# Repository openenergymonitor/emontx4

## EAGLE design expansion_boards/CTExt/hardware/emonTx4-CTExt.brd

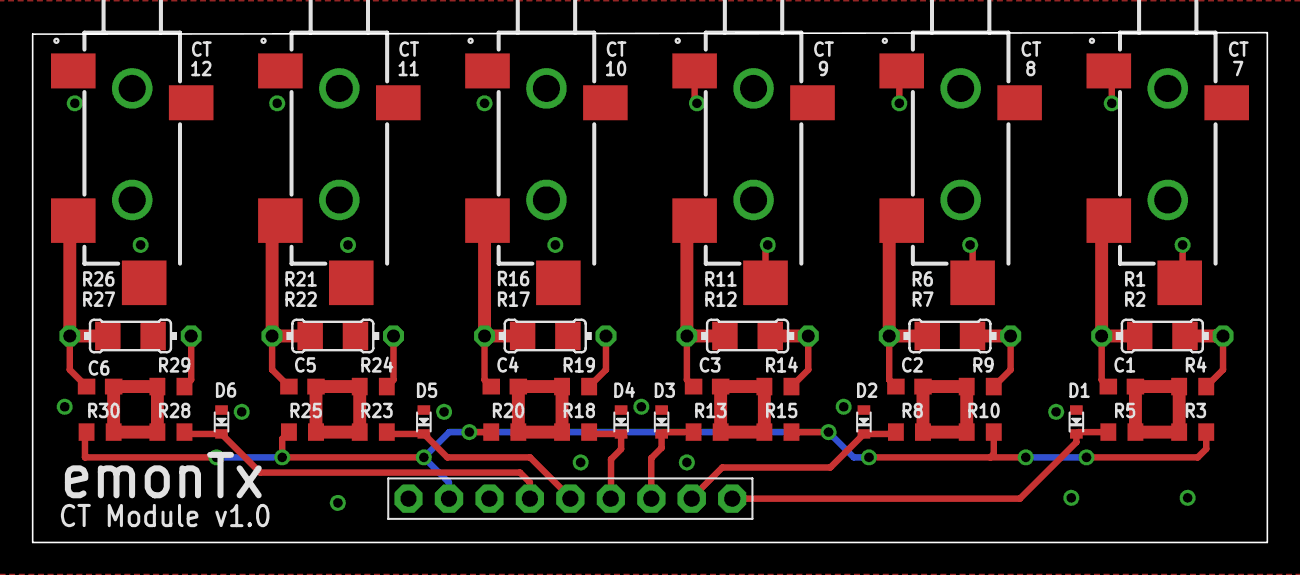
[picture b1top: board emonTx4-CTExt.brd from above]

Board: 2 copper layers, 77.5 x 32.0 mm, 49 parts (0 on the bottom side), 20 nets.

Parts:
ANALOG_EXPANDER: 1X09-BIG
C1, C2, C3, C4, C5, C6: 10uF 6V; C0603
D1, D2, D3, D4, D5, D6: ESD5Z3.3T1G; SOD-523
J1, J2, J3, J4, J7, J8: SJ-3524-SMT-TR
R1, R7, R12, R17, R22, R27: R1206
R2, R6, R11, R16, R21, R26: 0204/7
R3, R10, R15, R20, R25, R30: 180k; R0603
R4, R9, R14, R19, R24, R29: 33k; R0603
R5, R8, R13, R18, R23, R28: 1k; R0603

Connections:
3.3V: ANALOG_EXPANDER.2, R3.2, R10.2, R15.2, R20.2, R25.2, R30.2
AGND: ANALOG_EXPANDER.1, D1.A, D2.A, D3.A, D4.A, D5.A, D6.A, J1.1, J1.4, J2.1, J2.4, J3.1, J3.4, J4.1, J4.4, J7.1, J7.4, J8.1, J8.4, R1.1, R2.1, R4.2, R6.1, R7.1, R9.2, R11.1, R12.1, R14.2, R16.1, R17.1, R19.2, R21.1, R22.1, R24.2, R26.1, R27.1, R29.2
CT7: ANALOG_EXPANDER.9, D1.K, R5.2
CT8: ANALOG_EXPANDER.8, D2.K, R8.2
CT9: ANALOG_EXPANDER.7, D3.K, R13.2
CT10: ANALOG_EXPANDER.6, D4.K, R18.2
CT11: ANALOG_EXPANDER.5, D5.K, R23.2
CT12: ANALOG_EXPANDER.4, D6.K, R28.2
unnamed: C2.1, J2.2, R6.2, R7.2
unnamed: C2.2, R8.1, R9.1, R10.1
unnamed: C3.1, J4.2, R11.2, R12.2
unnamed: C3.2, R13.1, R14.1, R15.1
unnamed: C4.1, J7.2, R16.2, R17.2
unnamed: C4.2, R18.1, R19.1, R20.1
unnamed: C5.1, J8.2, R21.2, R22.2
unnamed: C5.2, R23.1, R24.1, R25.1
unnamed: C6.1, J3.2, R26.2, R27.2
unnamed: C6.2, R28.1, R29.1, R30.1
unnamed: C1.2, R3.1, R4.1, R5.1
unnamed: C1.1, J1.2, R1.2, R2.2

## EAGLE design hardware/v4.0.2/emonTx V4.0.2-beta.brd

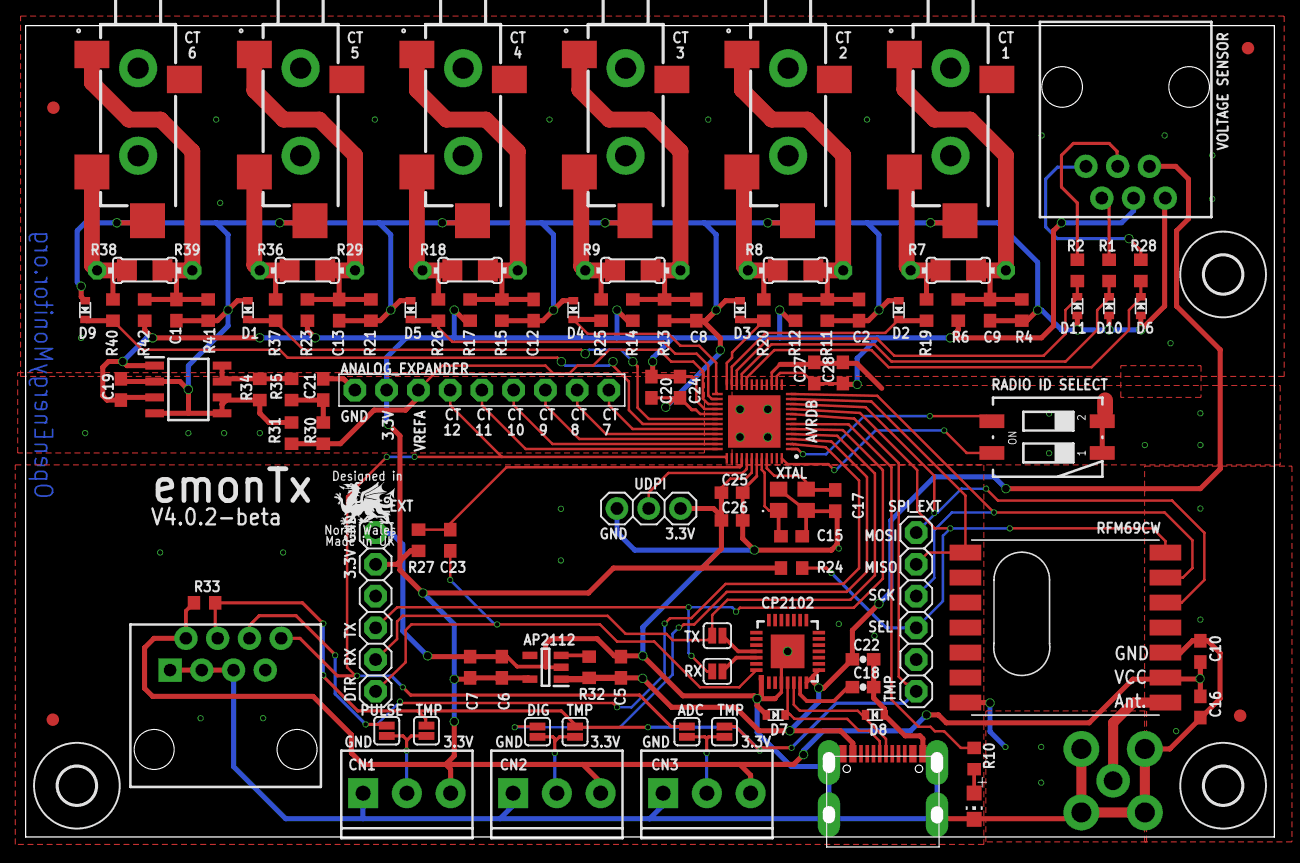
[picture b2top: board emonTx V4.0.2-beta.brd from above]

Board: 2 copper layers, 99.9 x 64.9 mm, 118 parts (1 on the bottom side), 65 nets.

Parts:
ANALOG_EXPANDER: 1X09-BIG
AP2112: AP2112K-3.3TRG1; SOT95P282X130-5N
AVRDB: AVR128DB48T-E_6LX; QFN40P600X600X90-49N
C1, C2, C8, C9, C12, C13: 10uF 6V; C0603
C5, C6: 1uF 6V; C0603
C7, C10, C20, C23, C25, C27: 100nF; C0603
C15, C17: 22pF; C0603
C16: 10uF; C0603
C18, C22: 100nF; 0603-CAP
C19, C21: 2.2uF; C0603
C24, C26, C28: 1uF; C0603
CN1, CN2, CN3: SCREWTERMINAL-3.5MM-3
CP2102: CP210X_USB_UART; MLP28
D1, D2, D3, D4, D5, D7, D8, D9: ESD5Z3.3T1G; SOD-523
D6, D10, D11: ESD; SOD-523
H2, H3, H4: MOUNT-HOLE3.0; 3,0
IC1: MCP1501-10E_SN; SOIC127P600X175-8N
J1, J2, J3, J4, J7, J8: SJ-3524-SMT-TR
J9: RJ11; RJ11-6
JP1: 1X06
LED1: Red 1.85V; CHIP-LED0805
LOGO1: OSHW_LOGO_6MILX0200-NT; OSHW_6X200_NOTEXT
R1, R2, R10, R28: 1K; R0603
R3, R5, R16, R22, R29, R38: 0204/7
R4, R11, R13, R15, R21, R41: 3.3k; R0603
R6, R12, R14, R17, R23, R42: 18k; R0603
R7, R8, R9, R18, R36, R39: R1206
R19, R20, R25, R26, R37, R40: 1k; R0603
R24: 120K; R0603
R27, R30, R31, R34: 10k; R0603
R32: 10K; R0603
R33: 4K7; R0603
R35: 10R; R0603
RX: SOLDERJUMPERNC; SJ_2S
S3: 2_SMT_DIP_SWITCH; DIP_SWITCH_SMT
SPI_EXT: 1X06
TX: SOLDERJUMPERNC; SJ_2S
TX_LINK1, TX_LINK2, TX_LINK3, TX_LINK4, TX_LINK5, TX_LINK6: SOLDERJUMPERNC; SJ_2S
U$1, U$4, U$5, U$7: FIDUCIAL; FIDUCIAL_1MM
U$13: RJ45-8PTH; RJ45-8
U$14: RFM12B
UDPI: 1X03
USB-C: CSP-USC16-TR; USB-C
X1: SMA90_DIP
XTAL: MCSJK-7U-12.00-12-10-80-B-10; MCSJK7U1200121080B10

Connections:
3.3V: ANALOG_EXPANDER.2, AP2112.5, AVRDB.14, AVRDB.28, AVRDB.42, C6.2, C7.2, C10.1, C16.1, C19.1, C20.1, C24.1, C25.1, C26.1, C27.1, C28.1, CN1.3, CN2.3, CN3.3, IC1.1, IC1.3, J9.3, JP1.5, R6.2, R12.2, R14.2, R17.2, R23.2, R24.2, R27.2, R33.1, R42.2, U$13.2, U$14.VDD, UDPI.3
+5V: AP2112.1, C5.2, C22.1, CP2102.7, CP2102.8, J9.2, R32.1, USB-C.A4/B9
AGND: ANALOG_EXPANDER.1, AVRDB.29, C1.2, C2.2, C8.2, C9.2, C12.2, C13.2, C19.2, C20.2, C21.2, C24.2, D1.A, D2.A, D3.A, D4.A, D5.A, D6.A, D9.A, D10.A, D11.A, IC1.2, IC1.4, IC1.5, IC1.6, J1.4, J2.4, J3.4, J4.4, J7.4, J8.4, J9.1, R4.2, R11.2, R13.2, R15.2, R21.2, R31.1, R34.1, R41.2
ANALOG_INPUT: ANALOG_EXPANDER.4, AVRDB.37, TX_LINK4.1, U$13.8
AVR_RX: AVRDB.5, JP1.3, RX.2
AVR_TX: AVRDB.4, JP1.2, TX.2
CT1: AVRDB.23, D2.K, R19.2
CT2: AVRDB.24, D3.K, R20.2
CT3: AVRDB.25, D4.K, R25.1
CT4: AVRDB.26, D5.K, R26.2
CT5: AVRDB.30, D1.K, R37.2
CT6: AVRDB.31, D9.K, R40.2
CT7: ANALOG_EXPANDER.9, AVRDB.32
CT8: ANALOG_EXPANDER.8, AVRDB.33
CT9: ANALOG_EXPANDER.7, AVRDB.34
CT10: ANALOG_EXPANDER.6, AVRDB.35
CT11: ANALOG_EXPANDER.5, AVRDB.36
D+: CP2102.4, D7.K, USB-C.A6
D-: CP2102.5, D8.K, USB-C.A7
DIG1: U$14.ANT, X1.ANTENNA
DIGITAL: AVRDB.3, TX_LINK5.1
DS18B20: AVRDB.8, R33.2, SPI_EXT.1, TX_LINK1.1, TX_LINK2.1, TX_LINK3.1, U$13.4
DTR: C23.1, CP2102.28, JP1.1
GND: AP2112.2, AVRDB.15, AVRDB.43, AVRDB.49, C5.1, C6.1, C7.1, C10.2, C15.2, C16.2, C17.2, C18.2, C22.2, C25.2, C26.2, C27.2, C28.2, CN1.1, CN2.1, CN3.1, CP2102.3, CP2102.EXP, CP2102.M, D7.A, D8.A, JP1.6, LED1.C, S3.1, S3.2, U$13.1, U$13.3, U$13.5, U$14.GND, U$14.P$12, UDPI.1, USB-C.A1/B12, USB-C.B1/A12, USB-C.GND1, USB-C.GND2, USB-C.GND3, USB-C.GND4, X1.GND1, X1.GND2, X1.GND3, X1.GND4, XTAL.2, XTAL.4
LED: AVRDB.6, R10.2
unnamed: AP2112.3, R32.2
unnamed: J3.2, R38.2, R39.2, R40.1
unnamed: J4.2, R9.2, R22.2, R25.2
unnamed: C18.1, CP2102.6
unnamed: C1.1, J3.1, R38.1, R39.1, R41.1, R42.1
unnamed: C21.1, R30.2, R35.1
unnamed: J7.2, R16.2, R18.2, R26.1
unnamed: J1.2, R5.2, R7.2, R19.1
unnamed: C9.1, J1.1, R4.1, R5.1, R6.1, R7.1
unnamed: J8.2, R29.2, R36.2, R37.1
unnamed: J2.2, R3.2, R8.2, R20.1
unnamed: CN1.2, TX_LINK1.2, TX_LINK6.2
unnamed: CN2.2, TX_LINK2.2, TX_LINK5.2
unnamed: CN3.2, TX_LINK3.2, TX_LINK4.2
unnamed: C2.1, J2.1, R3.1, R8.1, R11.1, R12.1
unnamed: C8.1, J4.1, R9.1, R13.1, R14.1, R22.1
unnamed: C12.1, J7.1, R15.1, R16.1, R17.1, R18.1
unnamed: IC1.7, IC1.8, R34.2, R35.2
unnamed: C13.1, J8.1, R21.1, R23.1, R29.1, R36.1
unnamed: LED1.A, R10.1
PULSE_INPUT: AVRDB.2, TX_LINK6.1, U$13.6
RESET: AVRDB.40, C23.2, R27.1
RFM_MISO: AVRDB.11, SPI_EXT.5, U$14.SDO
RFM_MOSI: AVRDB.10, SPI_EXT.6, U$14.SDI
RFM_SCK: AVRDB.12, SPI_EXT.4, U$14.SCK
RFM_SEL: AVRDB.9, R24.1, SPI_EXT.3, U$14.SEL
SWITCH1: AVRDB.48, S3.4
SWITCH2: AVRDB.1, S3.3
UDPI: AVRDB.41, UDPI.2
USB_RXD: CP2102.25, TX.1
USB_TXD: CP2102.26, RX.1
VREFA: ANALOG_EXPANDER.3, AVRDB.27, R30.1, R31.2
VS1: J9.6, R28.2
VS2: J9.5, R1.2
VS3: J9.4, R2.2
VSENS1: AVRDB.20, D6.K, R28.1
VSENS2: AVRDB.21, D10.K, R1.1
VSENS3: AVRDB.22, D11.K, R2.1
XTALHF1: AVRDB.44, C15.1, XTAL.1
XTALHF2: AVRDB.45, C17.1, XTAL.3

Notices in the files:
parts and their libraries:
microbuilder: This work is placed in the public domain, and may be freely used for commercial and non-commercial work with the following conditions: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
SparkFun-DigitalIC: Licensing: CC v3.0 Share-Alike You are welcome to use this library for commercial purposes.
